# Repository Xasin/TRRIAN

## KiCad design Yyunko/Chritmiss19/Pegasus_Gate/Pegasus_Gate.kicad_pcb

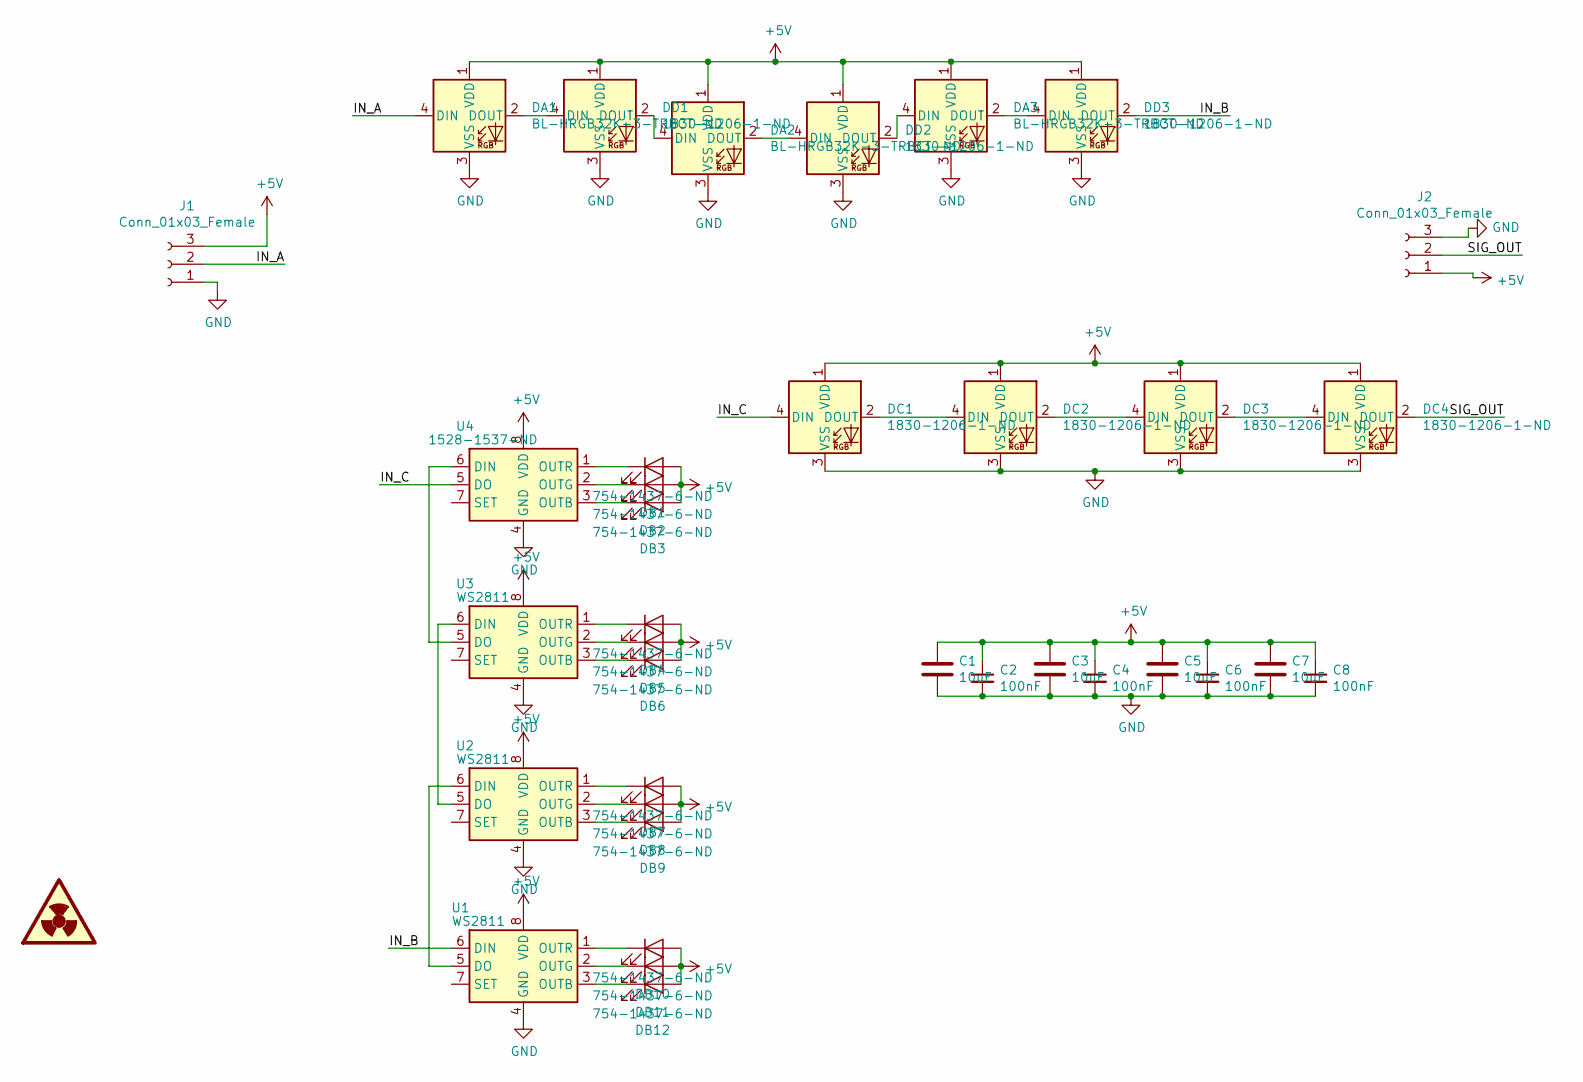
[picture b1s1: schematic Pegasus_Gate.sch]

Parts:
C1, C3, C5, C7: 10uF; C_0805_2012Metric
C2, C4, C6, C8: 100nF; C_0805_2012Metric
DA1, DA2, DA3: BL-HRGB32K-3-TRBCT-ND; LED_WS2812B_PLCC4_5.0x5.0mm_P3.2mm
DB1, DB2, DB3, DB4, DB5, DB6, DB7, DB8, DB9, DB10, DB11, DB12: 754-1437-6-ND; LED_0805_2012Metric_Castellated
DC1, DC2, DC3, DC4: 1830-1206-1-ND; IN-PI42TAS
DD1, DD2, DD3: 1830-1206-1-ND; IN-PI42TAS
J1, J2: Conn_01x03_Female; PinHeader_1x03_P2.54mm_Vertical
SYM1: SYM_Radioactive_Large; DragonIcon
U1, U2, U3: WS2811; SSOP-8_3.95x5.21x3.27mm_P1.27mm
U4: 1528-1537-ND; SSOP-8_3.95x5.21x3.27mm_P1.27mm

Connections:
+5V: C1.1, C2.1, C3.1, C4.1, C5.1, C6.1, C7.1, C8.1, DA1.1 (VDD), DA2.1 (VDD), DA3.1 (VDD), DB1.2 (A), DB2.2 (A), DB3.2 (A), DB4.2 (A), DB5.2 (A), DB6.2 (A), DB7.2 (A), DB8.2 (A), DB9.2 (A), DB10.2 (A), DB11.2 (A), DB12.2 (A), DC1.1 (VDD), DC2.1 (VDD), DC3.1 (VDD), DC4.1 (VDD), DD1.1 (VDD), DD2.1 (VDD), DD3.1 (VDD), J1.3, J2.1, U1.8 (VDD), U2.8 (VDD), U3.8 (VDD), U4.8 (VDD)
/IN_A: DA1.4 (DIN), J1.2
/IN_B: DD3.2 (DOUT), U1.6 (DIN)
/IN_C: DC1.4 (DIN), U4.5 (DO)
/SIG_OUT: DC4.2 (DOUT), J2.2
GND: C1.2, C2.2, C3.2, C4.2, C5.2, C6.2, C7.2, C8.2, DA1.3 (VSS), DA2.3 (VSS), DA3.3 (VSS), DC1.3 (VSS), DC2.3 (VSS), DC3.3 (VSS), DC4.3 (VSS), DD1.3 (VSS), DD2.3 (VSS), DD3.3 (VSS), J1.1, J2.3, U1.4 (GND), U2.4 (GND), U3.4 (GND), U4.4 (GND)
unnamed: DA1.2 (DOUT), DD1.4 (DIN)
unnamed: DA2.2 (DOUT), DD2.4 (DIN)
unnamed: DA2.4 (DIN), DD1.2 (DOUT)
unnamed: DA3.2 (DOUT), DD3.4 (DIN)
unnamed: DA3.4 (DIN), DD2.2 (DOUT)
unnamed: DB1.1 (K), U4.1 (OUTR)
unnamed: DB2.1 (K), U4.2 (OUTG)
unnamed: DB3.1 (K), U4.3 (OUTB)
unnamed: DB4.1 (K), U3.1 (OUTR)
unnamed: DB5.1 (K), U3.2 (OUTG)
unnamed: DB6.1 (K), U3.3 (OUTB)
unnamed: DB7.1 (K), U2.1 (OUTR)
unnamed: DB8.1 (K), U2.2 (OUTG)
unnamed: DB9.1 (K), U2.3 (OUTB)
unnamed: DB10.1 (K), U1.1 (OUTR)
unnamed: DB11.1 (K), U1.2 (OUTG)
unnamed: DB12.1 (K), U1.3 (OUTB)
unnamed: DC1.2 (DOUT), DC2.4 (DIN)
unnamed: DC2.2 (DOUT), DC3.4 (DIN)
unnamed: DC3.2 (DOUT), DC4.4 (DIN)
unnamed: U1.5 (DO), U2.6 (DIN)
unnamed: U2.5 (DO), U3.6 (DIN)
unnamed: U3.5 (DO), U4.6 (DIN)

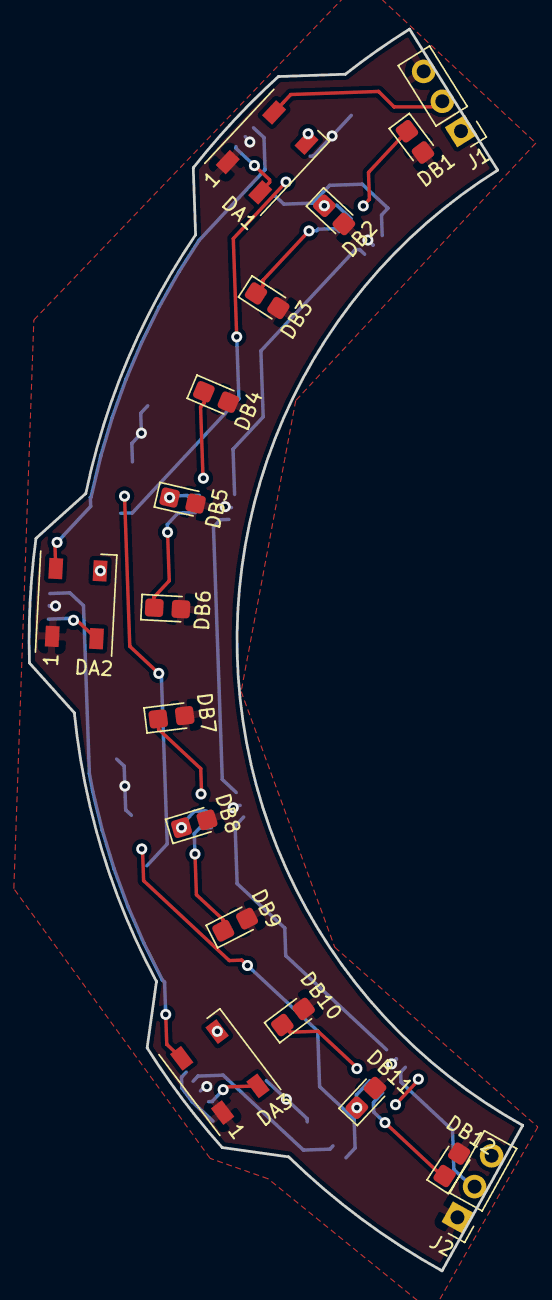
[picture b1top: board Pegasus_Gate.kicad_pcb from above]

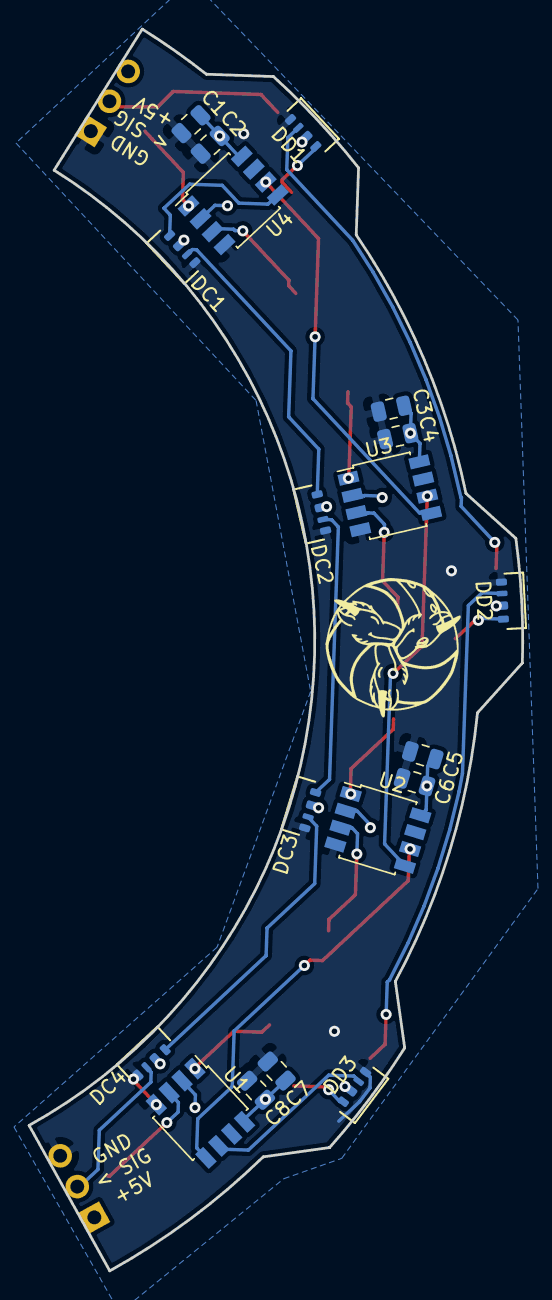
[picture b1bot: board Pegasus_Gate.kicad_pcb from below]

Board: 2 copper layers, 35.6 x 89.6 mm, 37 parts (20 on the bottom side), 29 nets.

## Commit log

2016-04-05 Added a first file with arduino communication things.
2016-04-05 Renamed file for cleaner structure.
2016-04-05 Removed 'main' function junk and cleaned a little.
2016-04-06 Fixed the coms, added timeout-based packets, etc. etc.
2016-04-06 Fixed timeout detection and added baudrate settings
2016-04-06 Added a separate window class ... Needs cleanup.
2016-04-06 Added new files and stuff!
2016-04-06 Added (somewhat) proper automated adding.
2016-04-06 More tweaks?
2016-04-09 Changed stuff, also added a 'compile.sh' script for automatic compilation.
2016-04-09 Added board outline & mounting hole files.
2016-04-09 Added a first basic thing :3
2016-04-09 Finalised the casing. Hope it works!
2016-04-09 Tweaked the mount holes to go all the way through.
2016-04-09 Tweaked the USB connections
2016-04-10 Bigger holes. Again.
2016-04-11 Added a 1.5mm thickness model for all dem tators out there :D
2016-04-16 Added a newer, simpler and hopefully better printer cooler!
2016-04-16 Added a print-cooler mount model!
2016-04-16 Placed the fan a bit lower!
2016-04-18 Added a model to block airflow to the fan, to further reduce its power
2016-05-16 Added a model for a /proper/ filament spool holder. Well, proper-ish, once I get the PTFE Tube.
2016-05-21 Added some stuff to hold the bowden Tube in place! :D
2016-06-05 Various 3D printer related models.
2016-06-05 Scematics!
2016-06-05 New Bottles pneumatic system!
2016-06-29 Added some files for a LUA based Factorio pathfinder. Random, still in work!
2016-06-29 Completely new map system with various interfacing functions!
2016-07-01 Lots of changes and restructures. Need to comment more clearly soongit add LUA/FactorioLayout/piecelist.lua
2016-07-01 Changed the dir_offset function to use elseif instead of math sin/cos calculations.
2016-07-01 Fixed the rotation of the dir_offset function return.\n It had the sinus values for up and down inverted.
2016-07-03 Small tweaks to the timings etc.
2016-07-03 First addition of a separate routes system, with enhanced functions and cleaner interfacing!
2016-07-03 Removed a conflicting function-names problem (Added 'local' to 'get_route')
2016-07-03 Added a function to get the absolute minimum heuristic.
2016-07-12 Not even sure what I did here o.o
2016-07-28 Random MOSFET Changes
2016-07-28 Initial commit of the sleek & nice cable chain design.
2016-07-29 Added ... Well, basically everything.
2016-07-29 Some small fixes to the clearing
2016-07-29 Made the clearing for the antislip bigger.
2016-07-29 Adjusted the intersection for the standing pieces to fit with the new clearing.
2016-07-29 Added antislip-wall configurations, small tweaks & gapSize configurability for open-inwards pieces.
2016-07-29 Resized the female connector filament hole to slip easier.
2016-07-30 Added a clip to used to, well, clip over the chain to secure wires in place.
2016-08-04 Started work on the OpenSCAD 'Tag-System' for enhaced 3D interaction.
2016-08-04 Addition of the first batch of tagging system.
2016-08-05 Small tweaks to the tag function that adds the new behavior (only show when called via show or if it is a foreground object), as well as adding in the basic Intersection, Difference and Union functio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
2016-08-06 Added more functionality to color and highlight objects!
    This thusly fixes #1 and completes the ToDo!
2016-08-08 Removed all the unneccesary 'demo' things.
2016-09-12 I ... Don't even know. Take it.
2017-03-23 Added Tupper Description <3
2017-03-23 Xas' ref pic
2017-03-23 Properly added ref file link
2018-11-11 First commit of glowy code :>
2018-11-12 Added the NeoPixel code
2018-11-12 First actually working version of the Layers code
2018-11-12 Added settings back, now well-configured
2018-11-13 Config diffs
2018-11-13 Tested out other layer methods
2018-11-13 Began to work on more animation stuff
2018-11-13 Added particle-based mane animation
2018-11-14 Began reworking animation structure
2018-11-15 Trying to separate continuous smoothing and animation
2018-11-15 Fixed modulo not wrapping around
2018-11-15 General test changes
2018-11-19 Value tuning and working on the real deal
2018-11-19 Added better color sets
2018-11-19 Trying to make WiFi work
2018-11-19 Got wifi working, more value tweaks
2018-11-24 Changed to 16bit colors <3
2018-11-24 Added alpha mod function
2018-11-24 Small fixes and adjustments
2018-11-28 Adjusted timing for the WS2812B
2018-11-28 Added touch detection class
2018-11-28 Used touch, new WiFi passwd storage
2018-11-28 TBH just playing around with this
2018-11-29 Fixed wrong write cmd
2018-11-29 Began working on a SSD1306 ESP class
2018-11-29 Working on the SSD code
2018-11-30 Added more SSD1306 functions
2018-11-30 Got me little LED workin <3
2018-12-04 Added a bigger font and some much-needed memory improvement ^^'
2018-12-04 REMOVE DEBUG
2018-12-04 Added a small console-like output, and a vprintf-like log output
2018-12-04 Moved components aside, began to add them to XasCode instead
2018-12-05 Changed a few things for the new XasCode library
2018-12-06 Tried out a new battery indicator icon
2018-12-06 Reworking battery icon
2018-12-07 Battery owo
2018-12-08 Fixed merge conflict
2018-12-08 Began working on a bit of cute 7-Segment code
2019-01-12 Finalized hedd
2019-03-15 Began working on a script for the MYS Guys
2019-08-08 Added fancy midi generator
2019-09-05 Began working on a cool KSP linked system :>
2019-11-27 Begin work on awesomerer gift
2019-11-27 Added sidemount LED footprint
2019-11-27 Almost sorted all secs out
2019-11-27 Continue work on PCB and Schematic
2019-11-28 Continue woork
2019-11-28 Begin work on assigning part nums
2019-11-29 Continue work on durg ring thing
2019-11-29 Smol changes and Gerbers
2019-12-02 Begin work on ESP32 code
2019-12-03 Continue work on cute stuff
2019-12-05 Let us test the new Color code
2019-12-24 Add and almost complete most gate files <3
2020-04-17 Smal change for LocaCI
2020-04-18 Add LocaCI Fail
2020-04-18 Poke run.rb to start test
2020-04-18 Made it fail
2020-04-18 Made it not fail
2020-04-18 Now it fails anew
2020-04-18 And no failing again
2020-04-18 No fail
2020-04-18 Actually fails more now
2020-04-18 Doesn't fail any more
2020-04-18 Wonder what this does
2020-04-18 Final not-fail
